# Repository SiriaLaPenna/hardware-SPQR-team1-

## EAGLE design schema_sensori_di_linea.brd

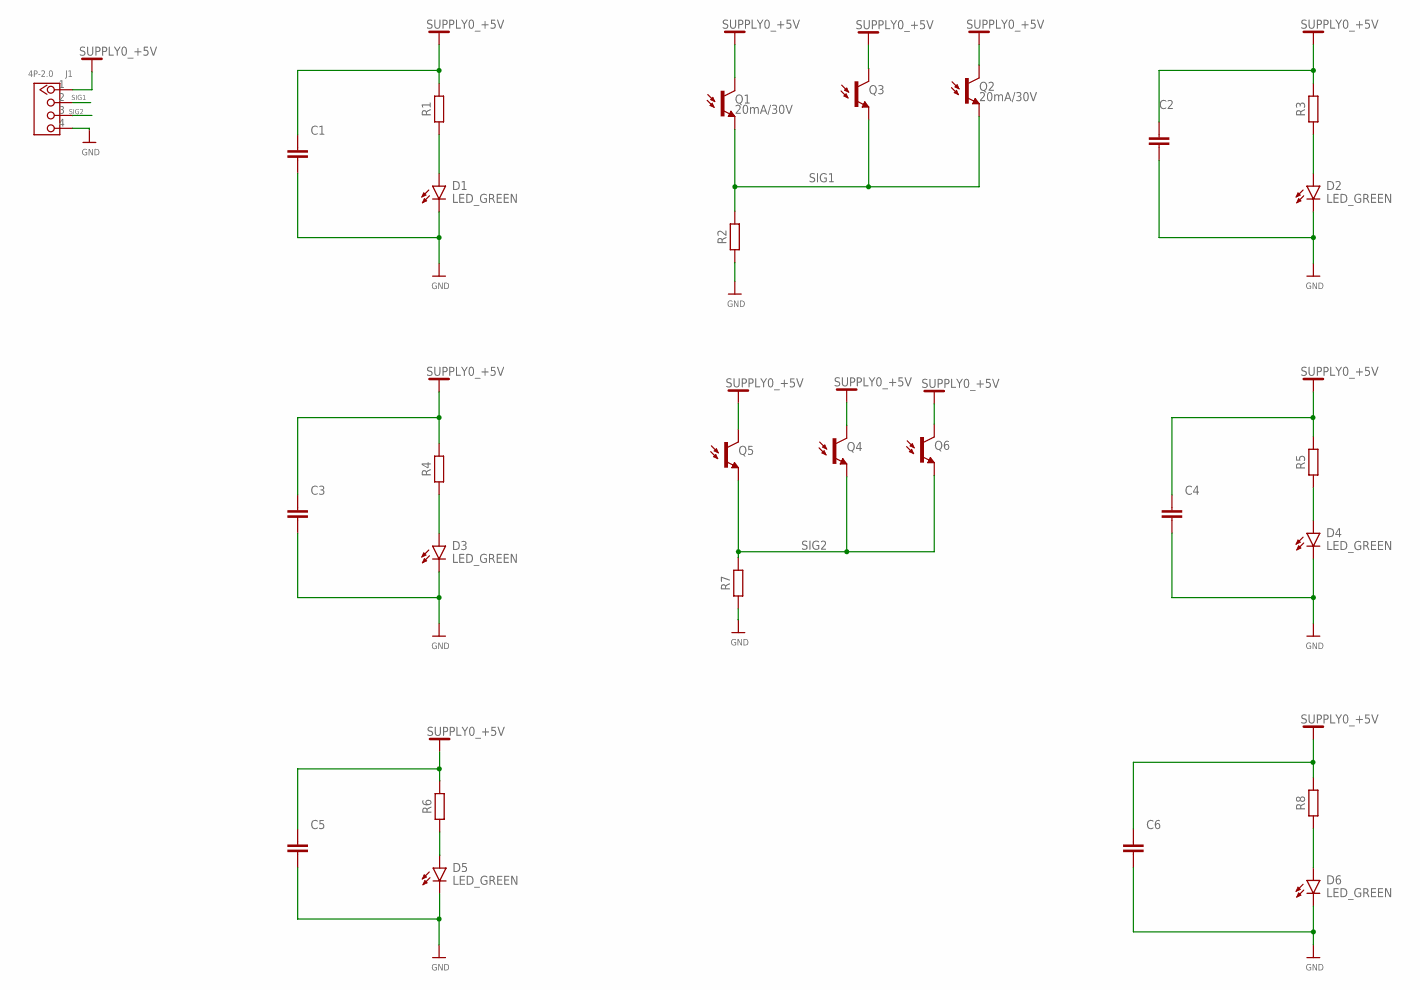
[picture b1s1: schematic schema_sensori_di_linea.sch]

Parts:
C1: 100nf; CAPC2012X110
C2, C3, C4, C5, C6: C_CHIP-0805(2012-METRIC); CAPC2012X110
D1, D2, D3, D4, D5, D6: LED_GREEN; LEDC2012X110N_FLAT-G
J1: 4P-2.0; HW4-2.0
Q1, Q2, Q3, Q4, Q5, Q6: 20mA/30V; PT17-21C-L41-TR8
R1: 330; RESC2012X65
R2, R3, R4, R5, R6, R7, R8: R_CHIP-0805(2012-METRIC); RESC2012X65

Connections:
+5V: C1.1, C2.1, C3.1, C4.1, C5.1, C6.1, J1.1, Q1.C, Q2.C, Q3.C, Q4.C, Q5.C, Q6.C, R1.2, R3.2, R4.2, R5.2, R6.2, R8.2
GND: C1.2, C2.2, C3.2, C4.2, C5.2, C6.2, D1.C, D2.C, D3.C, D4.C, D5.C, D6.C, J1.4, R2.1, R7.1
unnamed: D1.A, R1.1
unnamed: D2.A, R3.1
unnamed: D3.A, R4.1
unnamed: D4.A, R5.1
unnamed: D5.A, R6.1
unnamed: D6.A, R8.1
SIG1: J1.2, Q1.E, Q2.E, Q3.E, R2.2
SIG2: J1.3, Q4.E, Q5.E, Q6.E, R7.2

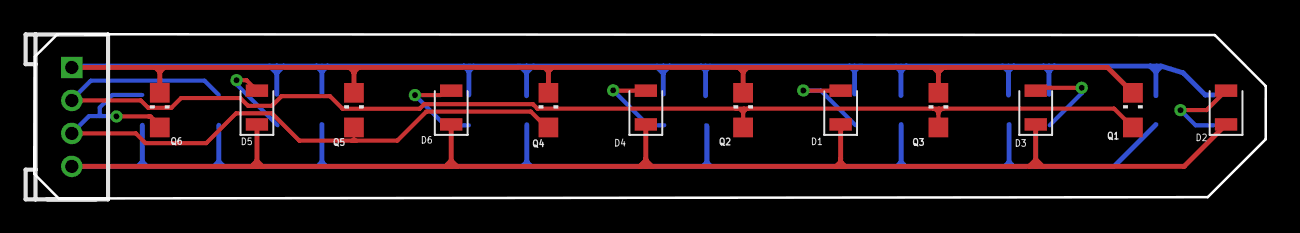
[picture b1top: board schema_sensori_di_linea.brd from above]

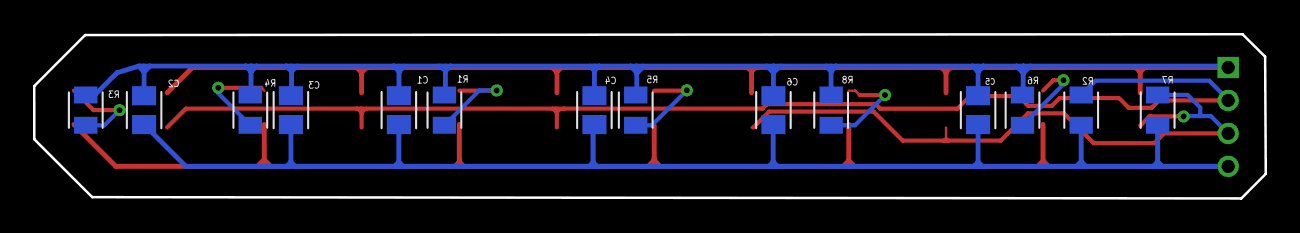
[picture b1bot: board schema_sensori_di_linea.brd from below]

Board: 2 copper layers, 74.7 x 10.0 mm, 27 parts (14 on the bottom side), 10 nets.

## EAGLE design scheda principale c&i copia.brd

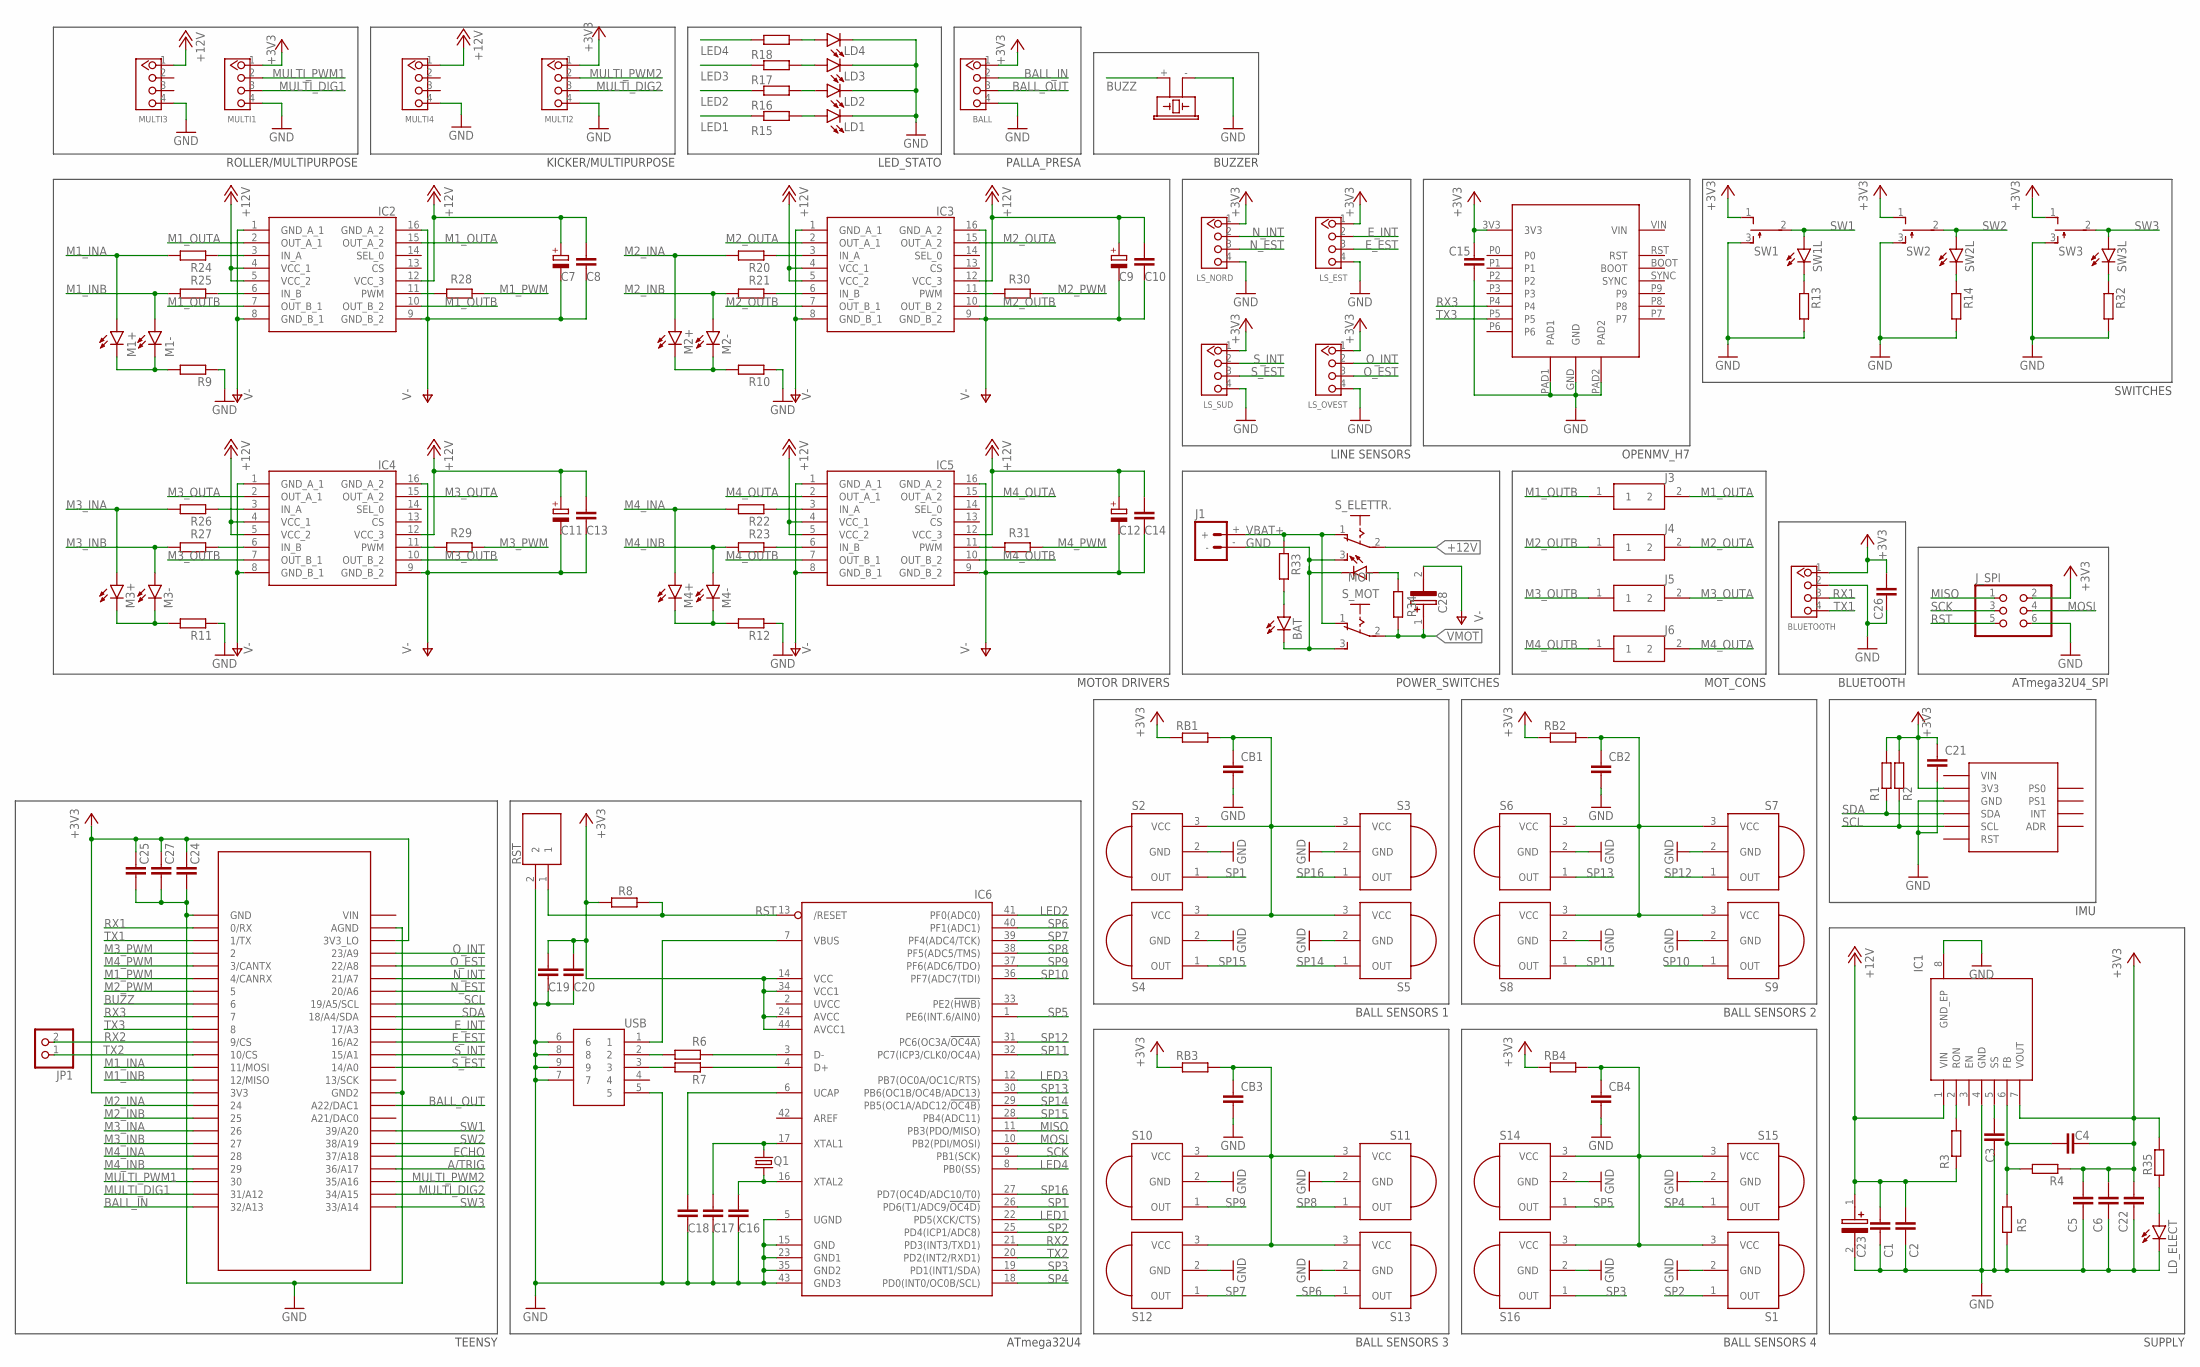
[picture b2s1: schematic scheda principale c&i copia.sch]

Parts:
BALL: TWIG_2.0; 2.0_1X4
BAT: LEDCHIPLED_1206; CHIPLED_1206
BLUETOOTH: TWIG_2.0; 2.0_1X4
BUZZER: F/CM12P
C1, C2, C22, C24, C27: 100n; C0805
C3, C4: 22n; C0805
C5, C6: 100u; C1206
C7: 1OOu; PANASONIC_E
C8, C10, C13, C14, C15, C16, C17, C18, C20, C21, C26: 1u; C0805
C9, C11, C12: 100u; PANASONIC_E
C19: 1u; C1206
C23, C28: EEV-FK1C152Q; FKV(H13)
C25: 100n; C1206
CB1, CB2, CB3, CB4: 0.1uF; C0805
IC1: LMZ14202TZE-ADJ_NOPB; NDW0007A
IC2, IC3, IC4, IC5: VNH7070ASTR; SOIC127P600X175-16N
IC6: ATMEGA32U4-AU; TQFP44
J1: BATTERY_CONN_DEANS; DEANS
J3, J4, J5, J6: 43650-0201; 43650-0200
JP1: PINHD-1X2; 1X02
J_SPI: PINHD-2X3; 2X03
LD1, LD2, LD3, LD4: LEDCHIPLED_1206; CHIPLED_1206
LD_ELECT: LEDCHIPLED_1206; CHIPLED_1206
LS_EST: TWIG_2.0; 2.0_1X4
LS_NORD: TWIG_2.0; 2.0_1X4
LS_OVEST: TWIG_2.0; 2.0_1X4
LS_SUD: TWIG_2.0; 2.0_1X4
M1+, M1-, M2+, M2-, M3+, M3-, M4+, M4-: LEDCHIPLED_1206; CHIPLED_1206
MOT: LEDCHIPLED_1206; CHIPLED_1206
MULTI1, MULTI2, MULTI3, MULTI4: TWIG_2.0; 2.0_1X4
Q1: CRYSTALHC49UP; HC49UP
R1, R2, R8: 10k; R0805
R3: 61,9k; R0805
R4: 3,32k; R0805
R5: 1,07k; R0805
R6, R7, R9, R10, R11, R12, R13, R14, R15, R16, R17, R18, R20, R21, R22, R23, R24, R25, R26, R27, R28, R29, R30, R31, R32, R33, R34, R35: R-EU_R0805; R0805
RB1, RB2, RB3, RB4: 22; R0805
RST: KSR231GLFS; KSR
S1, S2, S3, S4, S5, S6, S7, S8, S9, S10, S11, S12, S13, S14, S15, S16: PNA460XM
SW1, SW2, SW3: TL38PO; TL3XPO
SW1L, SW2L, SW3L: LEDCHIPLED_1206; CHIPLED_1206
S_ELETTR.: 255SB
S_MOT: 255SB
U$1: TEENSY_3.5/3.6
U$2: OPENMV_H7
U$4: BNO055
USB: 10104111-0001LF; 101041110001LF

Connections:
+3V3: BALL.1, BLUETOOTH.1, C4.2, C5.1, C6.1, C15.1, C19.1, C20.1, C21.1, C22.1, C24.1, C25.1, C26.1, C27.1, IC1.7 (VOUT), IC6.14 (VCC), IC6.24 (AVCC), IC6.34 (VCC1), IC6.44 (AVCC1), J_SPI.2, LS_EST.1, LS_NORD.1, LS_OVEST.1, LS_SUD.1, MULTI1.1, MULTI2.1, R1.2, R2.2, R4.1, R8.2, R35.2, RB1.1, RB2.1, RB3.1, RB4.1, SW1.1 (O), SW2.1 (O), SW3.1 (O), U$1.3V3, U$1.3V3_LO, U$2.3V3, U$4.3V3
+12V: C1.1, C2.1, C23.1 (+), IC1.1 (VIN), MULTI3.1, MULTI4.1, R3.1, S_ELETTR..2
A/TRIG: U$1.36/A17
BALL_IN: BALL.2, U$1.32/A13
BALL_OUT: BALL.3, U$1.A22/DAC1
BUZZ: BUZZER.+ (1), U$1.6
ECHO: U$1.37/A18
E_EST: LS_EST.3, U$1.16/A2
E_INT: LS_EST.2, U$1.17/A3
GND: BALL.4, BAT.C, BLUETOOTH.2, BUZZER.- (2), C1.2, C2.2, C3.2, C5.2, C6.2, C15.2, C16.2, C17.2, C18.2, C19.2, C20.2, C21.2, C22.2, C23.2 (-), C24.2, C25.2, C26.2, C27.2, CB1.2, CB2.2, CB3.2, CB4.2, IC1.4 (GND), IC1.8 (GND_EP), IC6.5 (UGND), IC6.15 (GND), IC6.23 (GND1), IC6.35 (GND2), IC6.43 (GND3), J1.-, J_SPI.6, LD1.C, LD2.C, LD3.C, LD4.C, LD_ELECT.C, LS_EST.4, LS_NORD.4, LS_OVEST.4, LS_SUD.4, MOT.C, MULTI1.4, MULTI2.4, MULTI3.4, MULTI4.4, R5.1, R9.1, R10.1, R11.1, R12.1, R13.2, R14.2, R32.2, RST.2, S1.2 (GND), S2.2 (GND), S3.2 (GND), S4.2 (GND), S5.2 (GND), S6.2 (GND), S7.2 (GND), S8.2 (GND), S9.2 (GND), S10.2 (GND), S11.2 (GND), S12.2 (GND), S13.2 (GND), S14.2 (GND), S15.2 (GND), S16.2 (GND), SW1.3 (S), SW2.3 (S), SW3.3 (S), S_ELETTR..3 (S), S_MOT.3 (S), U$1.AGND, U$1.GND, U$1.GND2, U$2.GND, U$2.PAD1, U$2.PAD2, U$4.GND, USB.5, USB.6, USB.7, USB.8, USB.9
INA_1: IC2.3 (IN_A), R24.1
INA_2: IC3.3 (IN_A), R20.1
INA_3: IC4.3 (IN_A), R26.1
INA_4: IC5.3 (IN_A), R22.1
INB_1: IC2.6 (IN_B), R25.1
INB_2: IC3.6 (IN_B), R21.1
INB_3: IC4.6 (IN_B), R27.1
INB_4: IC5.6 (IN_B), R23.1
LED1: IC6.22 (PD5(XCK/CTS)), R15.1
LED2: IC6.41 (PF0(ADC0)), R16.1
LED3: IC6.12 (PB7(OC0A/OC1C/RTS)), R17.1
LED4: IC6.8 (PB0(SS)), R18.1
M1_INA: M1+.A, R24.2, U$1.11/MOSI
M1_INB: M1-.A, R25.2, U$1.12/MISO
M1_OUTA: IC2.2 (OUT_A_1), IC2.15 (OUT_A_2), J3.2
M1_OUTB: IC2.7 (OUT_B_1), IC2.10 (OUT_B_2), J3.1
M1_PWM: R28.1, U$1.4/CANRX
M2_INA: M2+.A, R20.2, U$1.24
M2_INB: M2-.A, R21.2, U$1.25
M2_OUTA: IC3.2 (OUT_A_1), IC3.15 (OUT_A_2), J4.2
M2_OUTB: IC3.7 (OUT_B_1), IC3.10 (OUT_B_2), J4.1
M2_PWM: R30.1, U$1.5
M3_INA: M3+.A, R26.2, U$1.26
M3_INB: M3-.A, R27.2, U$1.27
M3_OUTA: IC4.2 (OUT_A_1), IC4.15 (OUT_A_2), J5.2
M3_OUTB: IC4.7 (OUT_B_1), IC4.10 (OUT_B_2), J5.1
M3_PWM: R29.1, U$1.2
M4_INA: M4+.A, R22.2, U$1.28
M4_INB: M4-.A, R23.2, U$1.29
M4_OUTA: IC5.2 (OUT_A_1), IC5.15 (OUT_A_2), J6.2
M4_OUTB: IC5.7 (OUT_B_1), IC5.10 (OUT_B_2), J6.1
M4_PWM: R31.1, U$1.3/CANTX
MISO: IC6.11 (PB3(PDO/MISO)), J_SPI.1
MOSI: IC6.10 (PB2(PDI/MOSI)), J_SPI.4
MULTI_DIG1: MULTI1.3, U$1.31/A12
MULTI_DIG2: MULTI2.3, U$1.34/A15
MULTI_PWM1: MULTI1.2, U$1.30
MULTI_PWM2: MULTI2.2, U$1.35/A16
unnamed: IC1.2 (RON), R3.2
unnamed: C4.1, IC1.6 (FB), R4.2, R5.2
unnamed: C3.1, IC1.5 (SS)
unnamed: LD4.A, R18.2
unnamed: C17.1, IC6.17 (XTAL1), Q1.2
unnamed: C16.1, IC6.16 (XTAL2), Q1.1
unnamed: C18.1, IC6.6 (UCAP)
unnamed: IC6.3 (D-), R6.1
unnamed: R6.2, USB.2
unnamed: R7.2, USB.3
unnamed: IC6.4 (D+), R7.1
unnamed: IC6.7 (VBUS), USB.1
unnamed: M2+.C, M2-.C, R10.2
unnamed: M1+.C, M1-.C, R9.2
unnamed: M3+.C, M3-.C, R11.2
unnamed: M4+.C, M4-.C, R12.2
unnamed: R13.1, SW1L.C
unnamed: R14.1, SW2L.C
unnamed: R32.1, SW3L.C
unnamed: LD1.A, R15.2
unnamed: LD2.A, R16.2
unnamed: LD3.A, R17.2
unnamed: BAT.A, R33.2
unnamed: MOT.A, R34.2
unnamed: LD_ELECT.A, R35.1
N_EST: LS_NORD.3, U$1.20/A6
N_INT: LS_NORD.2, U$1.21/A7
O_EST: LS_OVEST.3, U$1.22/A8
O_INT: LS_OVEST.2, U$1.23/A9
POWER_BLOCK_1: CB1.1, RB1.2, S2.3 (VCC), S3.3 (VCC), S4.3 (VCC), S5.3 (VCC)
POWER_BLOCK_2: CB2.1, RB2.2, S6.3 (VCC), S7.3 (VCC), S8.3 (VCC), S9.3 (VCC)
POWER_BLOCK_3: CB3.1, RB3.2, S10.3 (VCC), S11.3 (VCC), S12.3 (VCC), S13.3 (VCC)
POWER_BLOCK_4: CB4.1, RB4.2, S1.3 (VCC), S14.3 (VCC), S15.3 (VCC), S16.3 (VCC)
PWM3: IC4.11 (PWM), R29.2
PWM_1: IC2.11 (PWM), R28.2
PWM_2: IC3.11 (PWM), R30.2
PWM_4: IC5.11 (PWM), R31.2
RST: IC6.13 (/RESET), J_SPI.5, R8.1, RST.1
RX1: BLUETOOTH.3, U$1.0/RX
RX2: IC6.21 (PD3(INT3/TXD1)), JP1.2, U$1.9/CS
RX3: U$1.7, U$2.P4
SCK: IC6.9 (PB1(SCK)), J_SPI.3
SCL: R2.1, U$1.19/A5/SCL, U$4.SCL
SDA: R1.1, U$1.18/A4/SDA, U$4.SDA
SP1: IC6.26 (PD6(T1/ADC9/!OC4D)), S2.1 (OUT)
SP2: IC6.25 (PD4(ICP1/ADC8)), S1.1 (OUT)
SP3: IC6.19 (PD1(INT1/SDA)), S16.1 (OUT)
SP4: IC6.18 (PD0(INT0/OC0B/SCL)), S15.1 (OUT)
SP5: IC6.1 (PE6(INT.6/AIN0)), S14.1 (OUT)
SP6: IC6.40 (PF1(ADC1)), S13.1 (OUT)
SP7: IC6.39 (PF4(ADC4/TCK)), S12.1 (OUT)
SP8: IC6.38 (PF5(ADC5/TMS)), S11.1 (OUT)
SP9: IC6.37 (PF6(ADC6/TDO)), S10.1 (OUT)
SP10: IC6.36 (PF7(ADC7(TDI)), S9.1 (OUT)
SP11: IC6.32 (PC7(ICP3/CLK0/OC4A)), S8.1 (OUT)
SP12: IC6.31 (PC6(OC3A/!OC4A)), S7.1 (OUT)
SP13: IC6.30 (PB6(OC1B/OC4B/ADC13)), S6.1 (OUT)
SP14: IC6.29 (PB5(OC1A/ADC12/!OC4B)), S5.1 (OUT)
SP15: IC6.28 (PB4(ADC11)), S4.1 (OUT)
SP16: IC6.27 (PD7(OC4D/ADC10/T0)), S3.1 (OUT)
SW1: SW1.2, SW1L.A, U$1.39/A20
SW2: SW2.2, SW2L.A, U$1.38/A19
SW3: SW3.2, SW3L.A, U$1.33/A14
S_EST: LS_SUD.3, U$1.14/A0
S_INT: LS_SUD.2, U$1.15/A1
TX1: BLUETOOTH.4, U$1.1/TX
TX2: IC6.20 (PD2(INT2/RXD1)), JP1.1, U$1.10/CS
TX3: U$1.8, U$2.P5
V-: C7.-, C8.2, C9.-, C10.2, C11.-, C12.-, C13.2, C14.2, C28.2 (-), IC2.1 (GND_A_1), IC2.8 (GND_B_1), IC2.9 (GND_B_2), IC2.16 (GND_A_2), IC3.1 (GND_A_1), IC3.8 (GND_B_1), IC3.9 (GND_B_2), IC3.16 (GND_A_2), IC4.1 (GND_A_1), IC4.8 (GND_B_1), IC4.9 (GND_B_2), IC4.16 (GND_A_2), IC5.1 (GND_A_1), IC5.8 (GND_B_1), IC5.9 (GND_B_2), IC5.16 (GND_A_2)
VBAT+: J1.+, R33.1, S_ELETTR..1 (O), S_MOT.1 (O)
VMOT: C7.+, C8.1, C9.+, C10.1, C11.+, C12.+, C13.1, C14.1, C28.1 (+), IC2.4 (VCC_1), IC2.5 (VCC_2), IC2.12 (VCC_3), IC3.4 (VCC_1), IC3.5 (VCC_2), IC3.12 (VCC_3), IC4.4 (VCC_1), IC4.5 (VCC_2), IC4.12 (VCC_3), IC5.4 (VCC_1), IC5.5 (VCC_2), IC5.12 (VCC_3), R34.1, S_MOT.2

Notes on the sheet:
TEENSY
IMU
SUPPLY
POWER_SWITCHES
BALL SENSORS 1
BALL SENSORS 2
BALL SENSORS 3
BALL SENSORS 4
LINE SENSORS
MOTOR DRIVERS
OPENMV_H7
ATmega32U4
ATmega32U4_SPI
SWITCHES
BUZZER
LED_STATO
MOT_CONS
BLUETOOTH
ROLLER/MULTIPURPOSE
KICKER/MULTIPURPOSE
PALLA_PRESA

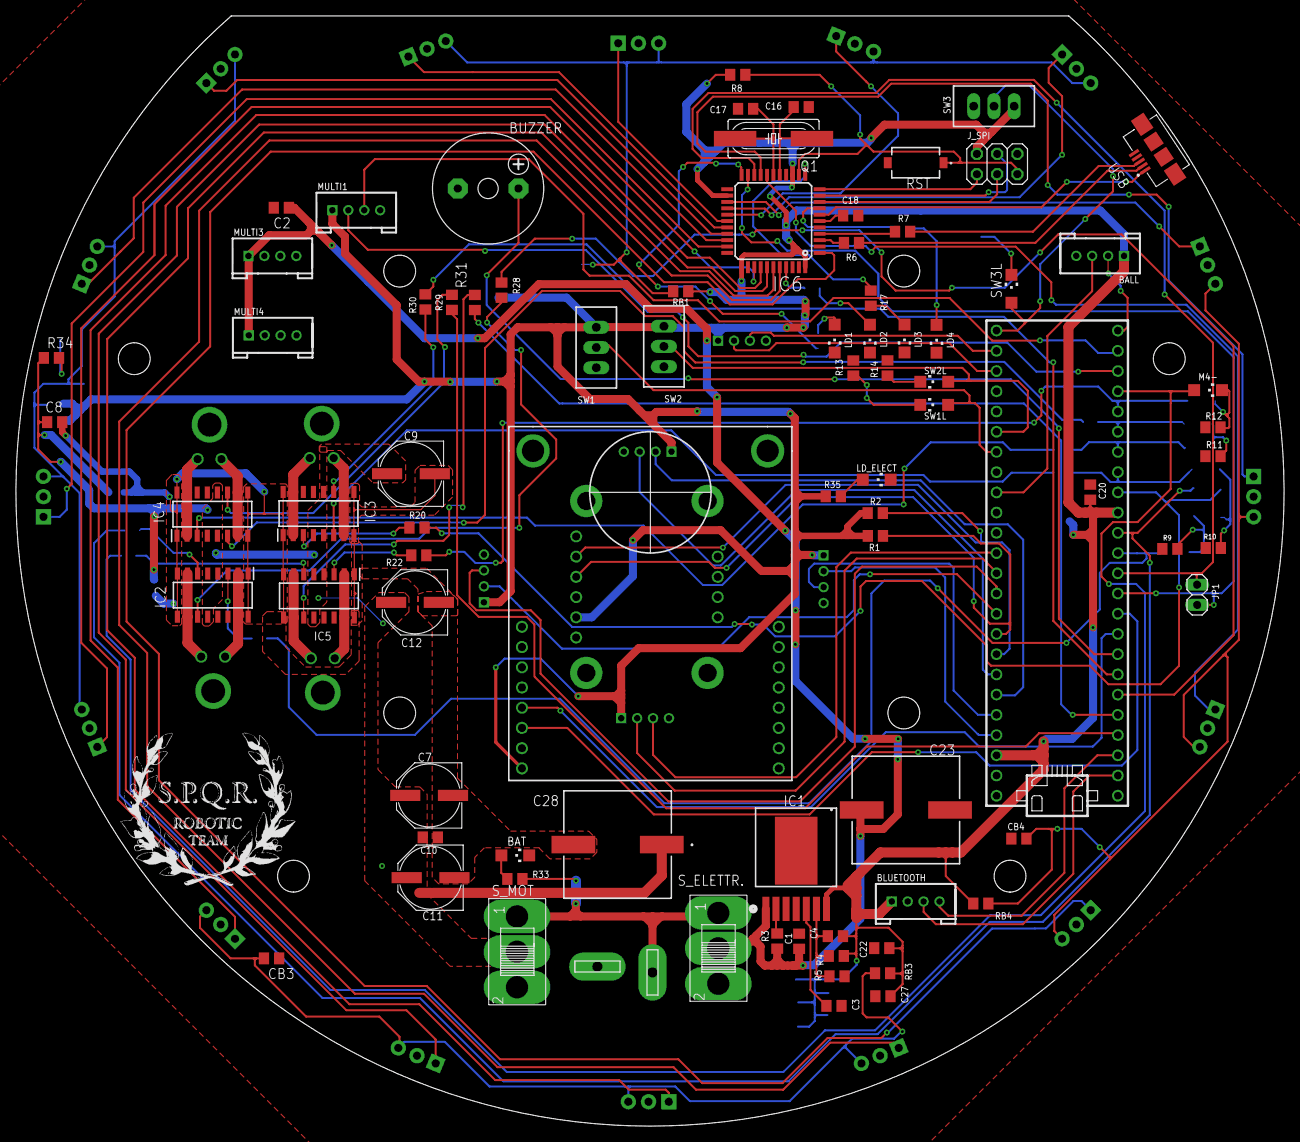
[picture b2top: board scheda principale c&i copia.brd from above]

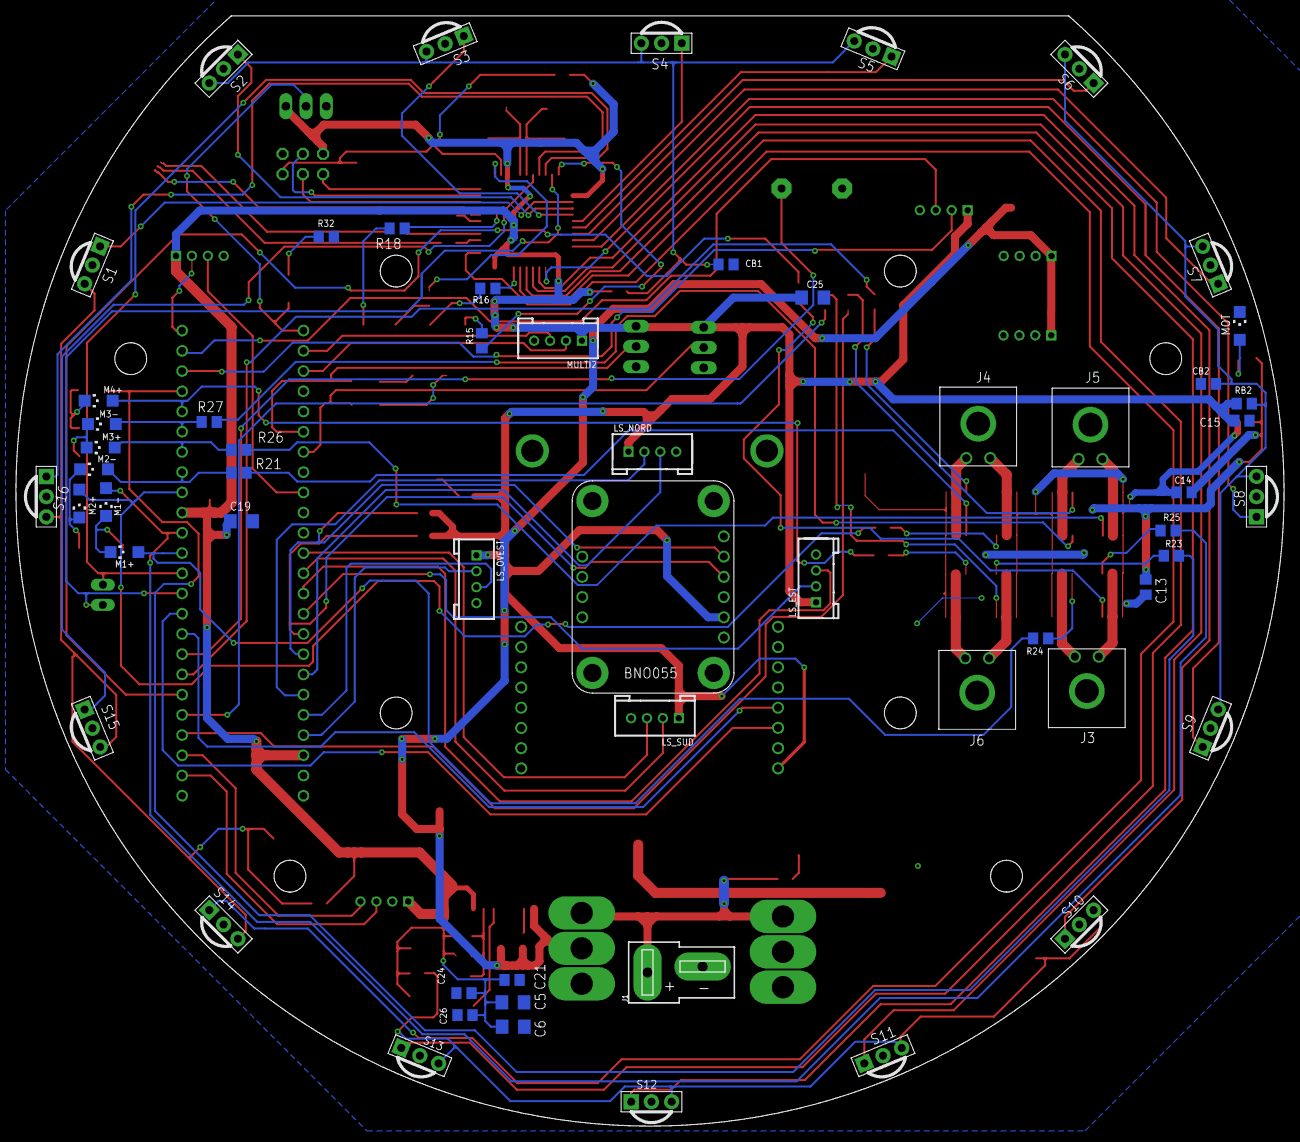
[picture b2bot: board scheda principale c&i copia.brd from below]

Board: 2 copper layers, 159.3 x 139.4 mm, 139 parts (58 on the bottom side), 117 nets.

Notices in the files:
parts and their libraries:
SparkFun-Connectors: Licensing: Creative Commons ShareAlike 4.0 International - https://creativecommons.org/licenses/by-sa/4.0
